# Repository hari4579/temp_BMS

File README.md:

# Distributed Battery Temperature Monitoring System

A modular, CAN-based temperature monitoring system developed for a **7.2 kWh, 40S12P battery pack**. The system uses distributed STM32-based temperature acquisition boards to monitor multiple locations across the battery pack and communicate temperature data to a central Battery Management System (BMS).

The architecture supports **75 NTC temperature-sensing channels**, combining five distributed monitoring boards with 13 channels each and 10 additional temperature-sensing points.

---

## 1. Project Overview

Battery temperature monitoring is essential for identifying thermal abnormalities and improving battery pack safety. This project implements a distributed temperature acquisition architecture to monitor temperatures across a high-capacity battery pack.

Instead of routing every thermistor signal to a single controller, temperature measurements are acquired locally by distributed microcontroller-based boards. Each board processes its NTC inputs, calculates temperature, performs fault checks, and transmits the acquired data over a CAN network.

### System Specifications

| Parameter | Specification |
|---|---|
| Battery pack energy | 7.2 kWh |
| Battery configuration | 40S12P |
| Total cell positions | 480 |
| Temperature-monitoring boards | 5 |
| NTC channels per board | 13 |
| Channels across five boards | 65 |
| Additional NTC sensors | 10 |
| **Total temperature-sensing channels** | **75** |
| Communication protocol | CAN |
| CAN bit rate | 500 kbps |
| Microcontroller | STM32F407VET6 |
| Temperature sensor | 10 kΩ NTC |

The 75 sensing points provide distributed temperature monitoring across the battery pack. The system does not assume one thermistor per cell.

## 2. System Architecture

The system follows a distributed temperature acquisition architecture.

Each temperature-monitoring board independently:
1. Acquires 13 NTC thermistor signals.
2. Converts ADC readings into thermistor resistance.
3. Calculates temperature using the Beta equation.
4. Checks for overtemperature and sensor faults.
5. Transmits temperature telemetry through CAN.

The distributed boards communicate with the central BMS controller over a shared CAN network.

### Architecture Diagram

```text
              7.2 kWh Battery Pack
                    40S12P
                       |
           Distributed NTC Sensors
                       |
       +---------------+---------------+
       |               |               |
       v               v               v
 +-----------+   +-----------+   +-----------+
 | Board 1   |   | Board 2   |   | Board 3   |
 | STM32     |   | STM32     |   | STM32     |
 | 13 NTC    |   | 13 NTC    |   | 13 NTC    |
 +-----------+   +-----------+   +-----------+
       |               |               |
       +---------------+---------------+
                       |
                 CAN Bus
                 500 kbps
                       |
       +---------------+---------------+
       |                               |
       v                               v
 +-----------+                   +-----------+
 | Board 4   |                   | Board 5   |
 | STM32     |                   | STM32     |
 | 13 NTC    |                   | 13 NTC    |
 +-----------+                   +-----------+
       |                               |
       +---------------+---------------+
                       |
                 CAN Network
                       |
                       v
             +------------------+
             | BMS Master       |
             | APARD32690       |
             +------------------+
                       |
                       v
              Battery Monitoring

       Additional temperature sensing:
                  10 NTC points

       Total system capacity: 75 channels
```

## 3. Hardware Design

### 3.1 Microcontroller – STM32F407VET6

Each temperature-monitoring board uses the STM32F407VET6 microcontroller.

Key features:
- ARM Cortex-M4 processor.
- 32-bit processing architecture.
- 12-bit ADC.
- Multiple communication peripherals.
- DMA support for ADC acquisition.
- SWD interface for programming and debugging.

The microcontroller handles thermistor acquisition, temperature conversion, fault detection, and CAN communication.

### 3.2 Temperature Sensing Circuit

The system uses MF55-series 10 kΩ NTC thermistors.

Each thermistor is connected through a voltage-divider circuit using a 10 kΩ reference resistor.

| Parameter | Value |
|---|---|
| Thermistor type | NTC |
| Thermistor resistance at 25°C | 10 kΩ |
| Reference resistor | 10 kΩ |
| Reference voltage | 3.3 V |
| ADC resolution | 12-bit |
| ADC channels per board | 13 |
| Number of boards | 5 |
| Additional sensors | 10 |
| Total sensing channels | 75 |

The analog voltage generated by each voltage divider is sampled by the STM32 ADC.

### 3.3 Temperature Calculation

The firmware converts ADC readings into resistance values and calculates temperature using the Beta equation.

\[
T=\left(\frac{1}{T_0}+\frac{1}{B}\ln\left(\frac{R}{R_0}\right)\right)^{-1}
\]

Where:

- \(T\) = Temperature in Kelvin.
- \(T_0\) = Reference temperature (298.15 K).
- \(B\) = Thermistor Beta coefficient (3950).
- \(R\) = Calculated thermistor resistance.
- \(R_0\) = Thermistor resistance at reference temperature (10 kΩ).

The calculated temperature is converted into Celsius for telemetry transmission.

### 3.4 Power Supply

The board receives a 5 V supply and uses a TLV75733 low-dropout regulator to generate the 3.3 V supply required by the microcontroller and associated circuitry.

### 3.5 CAN Communication

The TJA1051 CAN transceiver provides the physical interface between the STM32 and the CAN bus.

| Parameter | Configuration |
|---|---|
| CAN transceiver | TJA1051 |
| Communication protocol | CAN |
| Bit rate | 500 kbps |
| MCU logic supply | 3.3 V |
| Transceiver supply | 5 V |
| Termination | 120 Ω provision |

The distributed boards transmit temperature measurements to the central BMS controller through the shared CAN network.

---

## 4. PCB Design

The project includes two PCB revisions developed during the hardware design process.

### 4.1 V1 – Proof of Concept

The first PCB revision was developed to establish the hardware architecture and evaluate the initial circuit implementation.

Key design elements:
- STM32F407VET6-based temperature acquisition circuit.
- NTC voltage-divider interfaces.
- 5 V to 3.3 V power regulation.
- CAN transceiver circuitry.
- Test points for hardware measurements and debugging.

### 4.2 V2 – Revised PCB

The second revision represents the subsequent PCB design iteration.

It retains the distributed temperature acquisition architecture and incorporates updates made after the initial proof of concept.

The design integrates:
- STM32F407VET6 microcontroller.
- NTC sensing interfaces.
- Power regulation circuitry.
- CAN communication interface.
- Programming and debugging access.

### 4.3 Four-Layer PCB Stack-Up

The PCB uses a four-layer stack-up to organize signal routing, grounding, and power distribution.

| Layer | Function |
|---|---|
| L1 – Top | Component placement and signal routing |
| L2 – Inner 1 | Ground plane |
| L3 – Inner 2 | Power distribution |
| L4 – Bottom | Signal routing |

The dedicated ground and power layers provide reference planes and help organize routing for the mixed-signal design.

### 4.4 PCB Design Considerations

- Separation of analog temperature-sensing signals and digital circuitry.
- Ground-plane continuity and return-current paths.
- Power distribution for the MCU and CAN transceiver.
- SWD programming and debugging access.
- CAN bus routing and termination provisions.
- Test points for hardware bring-up and debugging.

---

## 5. Firmware Architecture

The firmware is developed using the STM32 Hardware Abstraction Layer (HAL).

The main firmware functions include:

1. ADC initialization and configuration.
2. DMA-based acquisition of 13 NTC channels.
3. ADC data buffering.
4. Conversion of ADC readings into thermistor resistance.
5. Temperature calculation using the Beta equation.
6. Overtemperature and sensor fault detection.
7. CAN telemetry generation and transmission.

### 5.1 ADC Acquisition

The STM32 ADC is configured for 13-channel scanning with DMA.

DMA transfers acquired ADC samples into a memory buffer, reducing the need for continuous CPU polling.

The firmware uses separate buffers to maintain and process acquired temperature data.

### 5.2 Fault Detection

The firmware includes checks for:

- Overtemperature conditions.
- NTC short-circuit conditions.
- NTC open-circuit conditions.

Overtemperature detection uses separate trip and clear thresholds, along with debounce logic, to avoid unnecessary fault triggering due to small measurement fluctuations.

The firmware defines fault codes for reporting the detected condition.

### 5.3 Temperature Telemetry

The firmware packs temperature readings into CAN frames.

Each temperature value is represented as a signed 16-bit fixed-point value, with a scaling factor of 100.

For example:

```text
Temperature:       25.50 °C
Transmitted value: 2550
```

The 13 channels are organized into four CAN frames:

| Frame | Temperature Channels | Payload |
|---|---|---|
| Frame 0 | CH0–CH3 | 8 bytes |
| Frame 1 | CH4–CH7 | 8 bytes |
| Frame 2 | CH8–CH11 | 8 bytes |
| Frame 3 | CH12 | 2 bytes |

The CAN identifier is generated using the board ID and frame index:

\[
CAN\ ID = 0x100 + (BOARD\_ID \times 0x10) + Frame
\]

This allows multiple temperature boards to share the same CAN network while maintaining separate message identifiers.

The firmware schedules telemetry transmission at 100 ms intervals.

### 5.4 CAN Fault Reporting

The firmware also defines fault-reporting messages.

Fault information includes:
- Board identification through the CAN arbitration ID.
- Thermistor channel identification.
- Fault type.

| Fault Code | Description |
|---|---|
| 0 | No fault |
| 1 | Overtemperature |
| 2 | Sensor short |
| 3 | Sensor open |

---

## 6. Repository Structure

```text
Temperature-Monitoring-System/
│
├── PCB/
│   ├── V1/
│   │   └── PCB design files
│   │
│   └── V2/
│       └── PCB design files
│
├── Firmware/
│   ├── Core/
│   │   ├── Inc/
│   │   └── Src/
│   │
│   └── STM32 project files
│
├── Documentation/
│   ├── Design_Report.pdf
│   └── Hardware documentation
│
└── README.md
```

*The directory structure is illustrative and should be adjusted to match the actual repository contents.*

---

## 7. Design Objectives

- Distributed acquisition of battery temperature measurements.
- Monitoring of 75 NTC temperature-sensing points.
- Modular hardware architecture.
- Local digitization of analog temperature signals.
- CAN-based communication with the central BMS.
- Scalable temperature monitoring across multiple battery locations.
- Detection of sensor faults and overtemperature conditions.
- Dedicated PCB design for temperature acquisition and communication.

## 8. Future Development

- Integration of all five temperature boards with the BMS master.
- Integration and documentation of the 10 additional temperature-sensing channels.
- Validation of temperature readings against calibrated reference measurements.
- CAN communication testing under multi-node operation.
- Hardware validation of sensor open-circuit and short-circuit detection.
- Integration of temperature fault information into BMS shutdown logic.
- Evaluation of communication reliability and timing under full system load.

## 9. Project Status

The project includes the temperature-monitoring hardware design, two PCB revisions, and STM32 firmware development.

The firmware implements ADC acquisition, NTC temperature conversion, fault detection logic, and CAN telemetry generation.

Full multi-board integration, additional sensor integration, and system-level validation remain development objectives.

## 10. Testing and Demonstration

A testing video demonstrating the temperature-monitoring system and its hardware operation is included below.

### Hardware Testing

The demonstration video showcases the hardware testing process and temperature-monitoring functionality.

**Testing Video:**

[TEMP_PoC.mp4](https://drive.google.com/file/d/1_f34zJ-By_HTeCJ9r7HJWei0OFtLDCeV/view?usp=drive_link)

The video provides a visual demonstration of the prototype during testing.
## Technologies Used

- **Microcontroller:** STM32F407VET6
- **Embedded Development:** Embedded C, STM32 HAL
- **Temperature Sensing:** 10 kΩ NTC thermistors
- **Analog Acquisition:** 12-bit ADC, DMA
- **Communication:** CAN, TJA1051
- **Power Regulation:** TLV75733
- **PCB Design:** Four-layer PCB
- **BMS Platform:** APARD32690, ADBMS6830

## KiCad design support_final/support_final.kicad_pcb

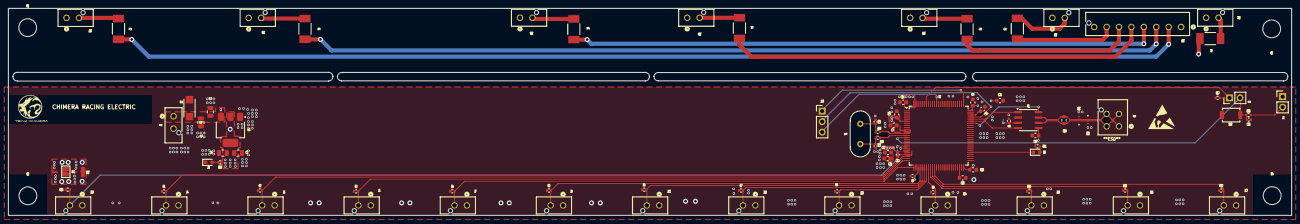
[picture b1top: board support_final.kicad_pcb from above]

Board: 4 copper layers, 310.0 x 50.0 mm, 91 parts (1 on the bottom side), 51 nets.

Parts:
C1, C4: 2.2uF X7R 0805; C_0805_2012Metric
C2: 1uF X7R 0805; C_0805_2012Metric
C3: 22uF X7R 0805; C_0805_2012Metric
C5, C7, C21: 4.7uF X7R 0603; C_0603_1608Metric
C6, C9, C13, C35: 0.1uF X7R 0402; C_0402_1005Metric
C8, C14, C15, C16, C18: 0.1uF X7R 0603; C_0603_1608Metric
C10, C11: 2.2uF X7R 0603; C_0603_1608Metric
C12: 1uF X7R 0603; C_0603_1608Metric
C19, C20: 20pF; C_0402_1005Metric
C34: 10uF X7R 0603; C_0603_1608Metric
CR1, CR2: PESD1CANFD36LS-QYL; PESD1
D1: LED 0603 BLUE; LED_0603_1608Metric
D2: 1N5819WS; diode
D3: LED 0603; LED_0603_1608Metric
F1, F2, F3, F4, F5, F6, F7: 0453.400MR; 0453Series_LTF
FB1: 80-120mohm (400mA -600mA) 0603 (BLM18AG121SN1D); BEADC1608X65N
H1, H2, H3, H4: MountingHole; MountingHole_4.3mm_M4
J1, J4, J5, J6, J7, J8, J11, J12, J13, J14, J15, J16, J17, J18, J21, J22, J23, J24, J25, J26, J27: Conn_01x02_Socket; microfit+_2
J2, J3: Conn_01x02_Pin; PinHeader_1x02_P2.54mm_Vertical
J9: Conn_01x04_Pin; CONN_2068320000-SD_04_MOL
J10: Conn_01x03_Socket; PinHeader_1x03_P2.54mm_Vertical
J20: Conn_01x08_Socket; CONN_2165710003-SD_08_MOL
JP1: SolderJumper_2_Open; SolderJumper-2_P1.3mm_Open_Pad1.0x1.5mm
R1, R2, R3, R4, R5, R6, R7, R8, R9, R10, R11, R12, R13, R17, R20: 10k 0402; R_0402_1005Metric
R15, R21: 330 ohms 0402; R_0402_1005Metric
R16: 120 ohms 0603; R_0603_1608Metric
R18: 0 ohms; R_0402_1005Metric
R19: 33 ohms; R_0402_1005Metric
SW2: SW_Push; SW_SPST_TS-1088-xR020
U1: TJA1051T-3; SOIC-8_3.9x4.9mm_P1.27mm
U2: STM32F446VETx; LQFP-100_14x14mm_P0.5mm
U4: AMS1117-3.3; SOT-223-3_TabPin2
Y1: 26MHz(YXC - HC-49US); Crystal_HC49-U_Vertical

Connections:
3.3V: C3.1, C4.1, C7.1, C8.1, C9.1, C14.1, C15.1, C16.1, C18.1, FB1.2, J2.2, JP1.1 (A), R15.1, R20.2, R21.1, U1.5 (VIO), U2.6 (VBAT), U2.11 (VDD), U2.19 (VDD), U2.28 (VDD), U2.50 (VDD), U2.75 (VDD), U2.100 (VDD), U4.2 (VO)
/MCU/BOOT0: J3.1, R17.2, U2.94 (BOOT0)
/MCU/RST: C35.1, J3.2, R20.1, SW2.2, U2.14 (NRST)
/MCU/SWCLK: J10.1, U2.76 (PA14)
/MCU/SWDIO: J10.2, U2.72 (PA13)
/MCU/SWO: J10.3, U2.89 (PB3)
/NTC/C1: F7.2, J20.2
/NTC/C1_f: F7.1, J27.2
/NTC/C2: F6.2, J20.3
/NTC/C2_f: F6.1, J26.2 (Pin_2_2)
/NTC/C3: F5.2, J20.4
/NTC/C3_f: F5.1, J25.2 (Pin_2_2)
/NTC/C4: F4.2, J20.5
/NTC/C4_f: F4.1, J24.2 (Pin_2_2)
/NTC/C5: F3.2, J20.6
/NTC/C5_f: F3.1, J23.2 (Pin_2_2)
/NTC/C6: F2.2, J20.7
/NTC/C6_f: F2.1, J22.2 (Pin_2_2)
/NTC/C7: F1.2, J20.8
/NTC/C7_f: F1.1, J21.2
/NTC/s_ground: J20.1, J21.1, J27.1
A0: J4.2, R1.2, U2.23 (PA0)
A1: J5.2, R2.2, U2.24 (PA1)
A2: J6.2, R3.2, U2.25 (PA2)
A3: J7.2, R4.2, U2.26 (PA3)
A4: J8.2, R5.2, U2.29 (PA4)
A5: J11.2, R6.2, U2.30 (PA5)
A6: J12.2, R7.2, U2.31 (PA6)
A7: J13.2, R8.2, U2.32 (PA7)
A8: J14.2, R9.2, U2.33 (PC4)
A9: J15.2, R10.2, U2.34 (PC5)
A10: J16.2, R11.2, U2.35 (PB0)
A11: J17.2, R12.2, U2.36 (PB1)
A12: J18.2, R13.2, U2.18 (PC3)
CAN_N: CR2.1, J9.1, J9.2, R16.2, U1.6 (CANL)
CAN_P: CR1.1, J9.3, J9.4, R16.1, U1.7 (CANH)
CAN_S: U1.8 (S), U2.69 (PA10)
CAN_rx: U1.4 (RXD), U2.70 (PA11)
CAN_tx: U1.1 (TXD), U2.71 (PA12)
GND: C1.2, C2.2, C3.2, C4.2, C5.2, C6.2, C7.2, C8.2, C9.2, C10.2, C11.2, C12.2, C13.2, C14.2, C15.2, C16.2, C18.2, C19.1, C20.1, C21.2, C34.2, C35.2, CR1.2, CR2.2, D1.1 (K), D2.2 (A), J1.2, J2.1, R1.1, R2.1, R3.1, R4.1, R5.1, R6.1, R7.1, R8.1, R9.1, R10.1, R11.1, R12.1, R13.1, R17.1, SW2.1, U1.2 (GND), U2.10 (VSS), U2.20 (VSSA), U2.27 (VSS), U2.49 (VSS), U2.74 (VSS), U2.99 (VSS), U4.1 (GND)
unnamed: C19.2, R18.1, Y1.2
unnamed: C20.2, R19.1, Y1.1
unnamed: D1.2 (A), R15.2
unnamed: D3.2 (A), R21.2
unnamed: D3.1 (K), U2.55 (PD8)
unnamed: R18.2, U2.12 (PH0)
unnamed: R19.2, U2.13 (PH1)
unnamed: C10.1, U2.48 (VCAP_1)
unnamed: C11.1, U2.73 (VCAP_2)
Vdda: C12.1, C13.1, C21.1, FB1.1, J4.1, J5.1, J6.1, J7.1, J8.1, J11.1, J12.1, J13.1, J14.1, J15.1, J16.1, J17.1, J18.1, JP1.2 (B), U2.21 (VREF+), U2.22 (VDDA)
Vin: C1.1, C2.1, C5.1, C6.1, C34.1, D2.1 (K), J1.1, U1.3 (VCC), U4.3 (VI)

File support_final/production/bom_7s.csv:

Designator,Footprint,Quantity,Value,LCSC Part #
"C1, C4",805,2,2.2uF X7R 0805,
"C10, C11",603,2,2.2uF X7R 0603,
C12,603,1,1uF X7R 0603,
"C13, C35, C6, C9",402,4,0.1uF X7R 0402,
"C14, C15, C16, C18, C8",603,5,0.1uF X7R 0603,
C2,805,1,1uF X7R 0805,
"C21, C5, C7",603,3,4.7uF X7R 0603,
C3,805,1,22uF X7R 0805,
C34,603,1,10uF X7R 0603,
D1,603,1,LED 0603 BLUE,
D2,diode,1,1N5819WS,
D3,603,1,LED 0603,
"F1, F2, F3, F4, F5, F6, F7",0453Series_LTF,7,0453.400MR,
"R1, R10, R11, R12, R13, R17, R2, R3, R4, R5, R6, R7, R8, R9",402,14,10k 0402,
"R15, R21",402,2,330 ohms 0402,
R16,603,1,120 ohms 0603,
SW2,SW_SPST_TS-1088-xR020,1,SW_Push,
U1,SOIC-8_3.9x4.9mm_P1.27mm,1,TJA1051T-3,
U2,LQFP-100_14x14mm_P0.5mm,1,STM32F446VETx,
U4,SOT-223-3_TabPin2,1,AMS1117-3.3,

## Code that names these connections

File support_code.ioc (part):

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Mcu.Name=STM32F446V(C-E)Tx
Mcu.Package=LQFP100
Mcu.UserName=STM32F446VETx
PA0-WKUP.Signal=ADCx_IN0
PA1.Signal=ADCx_IN1
PA10.Signal=GPIO_Output
PA11.Mode=CAN_Activate
PA11.Signal=CAN1_RX
PA12.Mode=CAN_Activate
PA12.Signal=CAN1_TX
PA13.Mode=JTAG_4_pins
PA13.Signal=SYS_JTMS-SWDIO
PA14.Mode=JTAG_4_pins
PA14.Signal=SYS_JTCK-SWCLK
PA15.Mode=JTAG_4_pins
PA15.Signal=SYS_JTDI
PA2.Signal=ADCx_IN2
PA3.Signal=ADCx_IN3
PA4.Signal=ADCx_IN4
PA5.Signal=ADCx_IN5
PA6.Signal=ADCx_IN6
PA7.Signal=ADCx_IN7
PB0.Signal=ADCx_IN8
PB1.Signal=ADCx_IN9
PB3.Mode=JTAG_4_pins
PB3.Signal=SYS_JTDO-SWO
PC0.Signal=ADCx_IN10
PC4.Signal=ADCx_IN14
PC5.Signal=ADCx_IN15
PD8.Signal=GPIO_Output
RCC.SYSCLKFreq_VALUE=180000000
RCC.SYSCLKSource=RCC_SYSCLKSOURCE_PLLCLK
board=custom
